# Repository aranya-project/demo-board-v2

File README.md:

# SpiderOak Demo V2 Board

This is a demonstration board for [Aranya
Embedded](https://github.com/aranya-project/aranya-embedded) built around the
ESP32-S3. It provides various peripheral options used by the [Aranya Embedded
demo](https://github.com/aranya-project/aranya-embedded/crates/demo-esp32-s3/).

## Board View

## Assembly Options

The IR transceiver U2 is necessary if you intend ot use IR networking. It uses
the Vishay TFBS4711 which is somewhat pricey, so it has not been included by
default.

The battery jack is a 2mm pitch JST PH connector, and the Qwiic connectors are
1mm pitch JST SH connectors. The RGB LED is a WS2812 5mm LED module. The SD card
slot is a SameSky MSD-4-A, and the USB jack is a GCT USB4105. If you search
around you will find many alternatives for these as they are very commonly used.

A footprint is provided but not populated for reset switch - a SMD 6mm tactile
switch (Omron B3FS or similar). Likewise there is an unpopulated 20pin expansion
header on the back - details on that [below](#test-points-and-expansion).

## Power

Input power comes from either the battery or the USB input. A schottky diode and
a P-channel MOSFET (D5 and Q1) switch power between them and prevent USB power
from backfeeding into the battery. The battery is charged by a standard 500mA
5-pin single-cell lithium linear charge controller (TPS4054/MCP73831/etc), and
LED D1 will light when charging is complete.

The ESP32 is powered by a primary 3.3V regulator (the TLV74333), and all other
devices (IR transceiver, SD card slot, and any Qwiic accessories) are powered
by a secondary 3.3V regulator enabled by a high output on GPIO 47.

Separately, power to the RGB LED is switched via an open drain output on GPIO
40. This pin must be brought low to turn on the P-channel MOSFET controlling
power to the LED. The LED power is connected to input power (either the USB or
battery) directly, so it is not controlled by the accessory power regulator.

### Pin Summary

| GPIO Pin | Function | Operation |
|----------|----------|-----------|
| 47 | Accessory power enable | output, active high |
| 40 | LED power enable | open drain output, active low |

## IR Transceivers

IR1 is connected to UART1 TX/RX on pins on GPIOs 13 and 14, respectively. The IR
transceiver has to be enabled with a low output on GPIO 21.

Enabling IrDA mode requires setting `UART_IRDA_EN` in `UART_CONF0_REG`.
Additionally, to transmit, you need to set `UART_IRDA_TX_EN`. By default, IrDA
mode is half duplex, and `UART_IRDA_TX_EN` needs to be toggled to switch between
transmit and receive modes. To enable both transmit and receive at the same
time, which will echo all transmitted data through the RX line, set
`UART_IRDA_DPLX`.

For reasons I don't understand, the only thing that can be set via IDF APIs is
enabling IrDA mode. All of the other IrDA settings are not available via IDF
APIs, so you will likely have to twiddle the registers directly. In C, this can
be done by including `soc/uart_struct.h` and using the bitfield structs
provided. e.g.

```
UART1.conf0.irda_dplx = 1;
```

### Pin Summary

| GPIO Pin | Function | Operation |
|----------|----------|-----------|
| 13 | Transmit | output |
| 14 | Receive | input |
| 21 | Enable | output, active low |

## Micro SD

The SD card is connected to SPI such that it should be usable directly
through the IOMUX on IOs 35, 36, and 37. CS is connected to GPIO 38.
The slot has card detect functionality, which is connected to GPIO 48.

Additionally, DAT1 and DAT2 (only used in SD mode) are connected to
GPIOs 45 and 39, respectively, so you should theoretically be able to
enable 4-bit SD through the SD/MMC controller.

### Pin Summary (SPI mode)

| GPIO Pin | Function | Operation |
|----------|----------|-----------|
| 36 | SCK | output |
| 35 | MOSI | output |
| 37 | MISO | input |
| 38 | CS | output |

### Pin Summary (SD 1-bit mode)

| GPIO Pin | Function | Operation |
|----------|----------|-----------|
| 36 | CLK | output |
| 35 | CMD | input/output |
| 37 | DAT0 | input/output |
| 38 | CD | input |

### Pin Summary (SD 4-bit mode)

| GPIO Pin | Function | Operation |
|----------|----------|-----------|
| 36 | CLK | output |
| 35 | CMD | input/output |
| 37 | DAT0 | input/output |
| 45 | DAT1 | input/output |
| 39 | DAT2 | input/output |
| 38 | DAT3 | input/output |

### Pin Summary (card detect)

| GPIO Pin | Function | Operation |
|----------|----------|-----------|
| 48 | card detect | input, pull-up, active low |

## Debug LEDs

Three LEDs are hooked up to GPIOs 10-12, and can be used for any purpose.

### Pin Summary

| GPIO Pin | Function | Operation |
|----------|----------|-----------|
| 10 | Debug LED 1 | output, active high |
| 11 | Debug LED 2 | output, active high |
| 12 | Debug LED 3 | output, active high |

## Test points and expansion

The unused GPIOs 1-3, 6-9, 15-18, 42, and 46; the debug LED GPIOs 10-12; as
well as the main and accessory 3.3V regulators; and GND are broken out via a
20-pin 1mm pitch flat flex footprint on the back. You can either install a flat
flex connector or wire directly to the pads.

Test points are provided for VBUS (USB power), V_IN (OR'd power between VBUS and
VBATT), main 3V3, V<sub>acc</sub> (accessory power), SCL/SDA connected to the
Qwiic ports, and SCK, MOSI, MISO, CS, DAT1, DAT2 and CD on the SD card slot.

A three-pin 0.1" header is available for TX, RX, and GND for UART0, and a single
pin header is available for the DO pin on the WS2812 LED module. There are also
0.1" pin headers for the reset switch inside the tactile switch footprint.

## Mechanical

The board is 68mm wide and 42mm tall (2.68 x 1.66 inches). The ESP32-S3 module's
antenna hangs off of the bottom of the board, making the full height 48.4mm
(1.91 inches).

At the top are two M5 sized plated holes meant to accomodate lanyard hooks. They
are centered 5mm from the edges. At the bottom are two more M2.5 holes for any
other mounting needs, centered 3mm from the edges.

A 7x4mm cutout is provided near the battery connector in the top right of the
board. This allows any battery cables to be routed below the board even if the
board is mounted flush against a case.

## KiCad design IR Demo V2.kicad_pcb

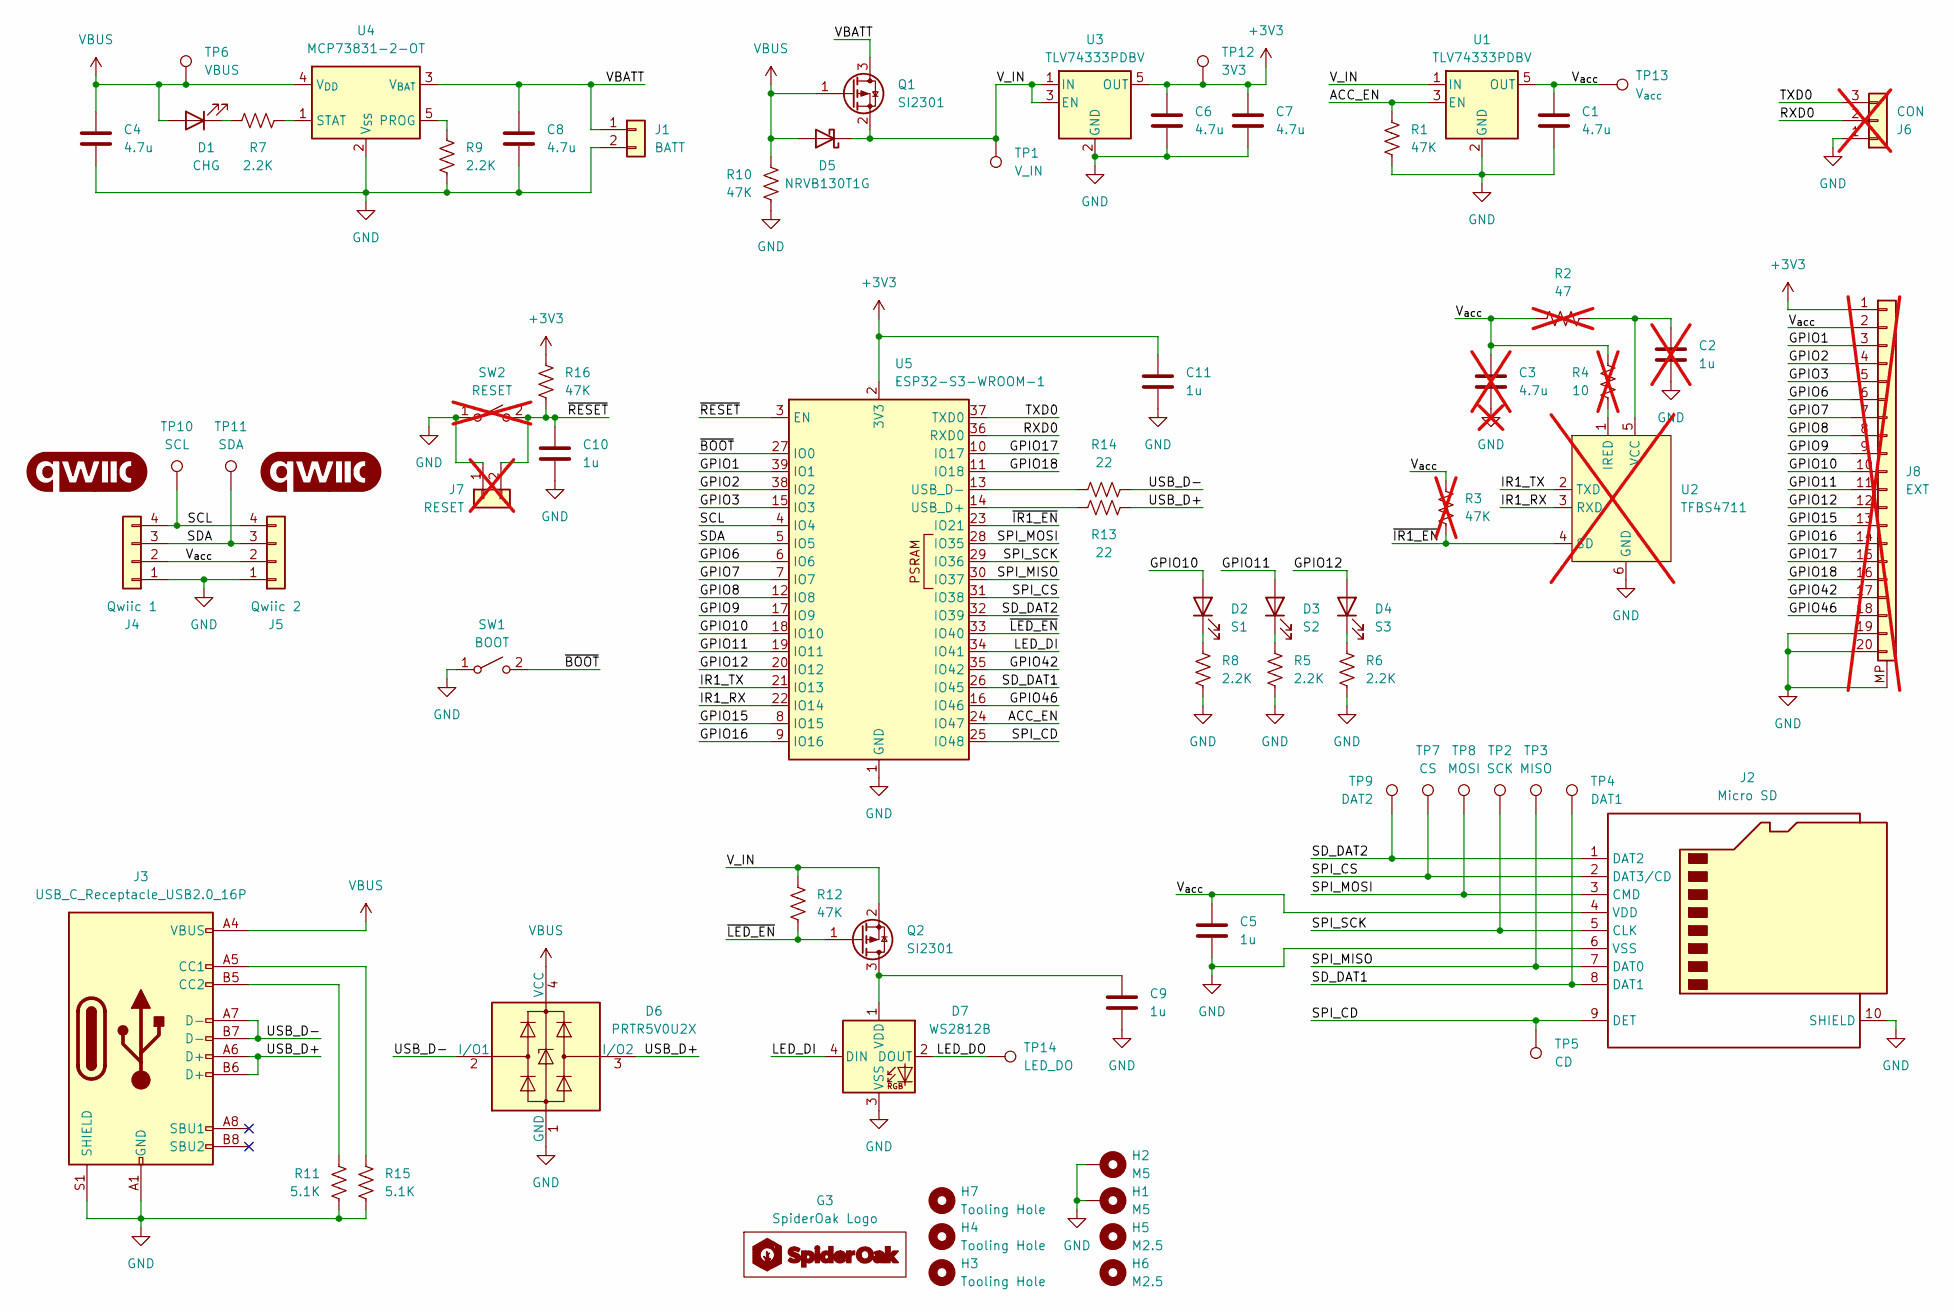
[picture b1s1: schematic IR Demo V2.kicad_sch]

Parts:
C1, C4, C6, C7, C8: 4.7u; C_0805_2012Metric_Pad1.18x1.45mm_HandSolder; MPN CL21A475KPFNNNG; LCSC PN C1779
C2: 1u; C_0805_2012Metric_Pad1.18x1.45mm_HandSolder; MPN CL21B105KBFNNNE; not fitted
C3: 4.7u; C_0805_2012Metric_Pad1.18x1.45mm_HandSolder; MPN CL21A475KPFNNNG; not fitted
C5, C9, C10, C11: 1u; C_0805_2012Metric_Pad1.18x1.45mm_HandSolder; MPN CL21B105KBFNNNE; LCSC PN C28323
D1: CHG; LED_0805_2012Metric; MPN XL-2012SURC; LCSC PN C965812
D2: S1; LED_0805_2012Metric; MPN XL-2012SURC; LCSC PN C965812
D3: S2; LED_0805_2012Metric; MPN XL-2012SURC; LCSC PN C965812
D4: S3; LED_0805_2012Metric; MPN XL-2012SURC; LCSC PN C965812
D5: NRVB130T1G; D_SOD-123; MPN NRVB130T1G; LCSC PN C917121
D6: PRTR5V0U2X; SOT-143; MPN PRTR5V0U2X; LCSC PN C558444
D7: WS2812B; LED_WS2812B_PLCC4_5.0x5.0mm_P3.2mm
G1, G2: qwiic_Logo; qwiic_5.5mm
G3: SpiderOak Logo; SpiderOak_Logo
H1, H2: M5; MountingHole_5.3mm_M5_DIN965_Pad
H3, H4, H7: Tooling Hole; ToolingHole_1.152mm
H5, H6: M2.5; MountingHole_2.7mm_M2.5
J1: BATT; JST_PH_S2B-PH-SM4-TB_1x02-1MP_P2.00mm_Horizontal; MPN WAFER-PH2.0-2PWB; LCSC PN C3029440
J2: Micro SD; MSD-4-A; MPN MSD-4-A; LCSC PN C5454948
J3: USB_C_Receptacle_USB2.0_16P; USB_C_Receptacle_GCT_USB4105-xx-A_16P_TopMnt_Horizontal; MPN USB4105; LCSC PN C2988369
J4: Qwiic 1; JST_SH_SM04B-SRSS-TB_1x04-1MP_P1.00mm_Horizontal; MPN WAFER-SH1.0-4PWB; LCSC PN C3029343
J5: Qwiic 2; JST_SH_SM04B-SRSS-TB_1x04-1MP_P1.00mm_Horizontal; MPN WAFER-SH1.0-4PWB; LCSC PN C3029343
J6: CON; PinHeader_1x03_P2.54mm_Vertical; not fitted
J7: RESET; PinHeader_1x02_P2.54mm_Vertical; not fitted
J8: EXT; TE_2-84953-0_1x20-1MP_P1.0mm_Horizontal; not fitted
Q1, Q2: SI2301; SOT-23; MPN SI2301; LCSC PN C42456911
R1, R10, R12, R16: 47K; R_0805_2012Metric_Pad1.20x1.40mm_HandSolder; MPN RC0805FR-0747KL; LCSC PN C126351
R2: 47; R_0805_2012Metric_Pad1.20x1.40mm_HandSolder; MPN RC0805FR-0722RL; not fitted
R3: 47K; R_0805_2012Metric_Pad1.20x1.40mm_HandSolder; MPN RC0805FR-0747KL; not fitted
R4: 10; R_0805_2012Metric_Pad1.20x1.40mm_HandSolder; MPN RC0805FR-0710RL; not fitted
R5, R6, R7, R8, R9: 2.2K; R_0805_2012Metric_Pad1.20x1.40mm_HandSolder; MPN RC0805FR-072K2L; LCSC PN C114561
R11, R15: 5.1K; R_0805_2012Metric_Pad1.20x1.40mm_HandSolder; MPN RC0805FR-075K1L; LCSC PN C84375
R13, R14: 22; R_0805_2012Metric_Pad1.20x1.40mm_HandSolder; MPN RC0805FR-0722RL; LCSC PN C107702
SW1: BOOT; SW_Push_1P1T_NO_CK_PTS125Sx43PSMTR; MPN TS-1003S-05026; LCSC PN C455219
SW2: RESET; SW_SPST_PTS645; not fitted
TP1: V_IN; TestPoint_Pad_D1.0mm
TP2: SCK; TestPoint_Pad_D1.0mm
TP3: MISO; TestPoint_Pad_D1.0mm
TP4: DAT1; TestPoint_Pad_D1.0mm
TP5: CD; TestPoint_Pad_D1.0mm
TP6: VBUS; TestPoint_Pad_D1.0mm
TP7: CS; TestPoint_Pad_D1.0mm
TP8: MOSI; TestPoint_Pad_D1.0mm
TP9: DAT2; TestPoint_Pad_D1.0mm
TP10: SCL; TestPoint_Pad_D1.0mm
TP11: SDA; TestPoint_Pad_D1.0mm
TP12: 3V3; TestPoint_Pad_D1.0mm
TP13: V_{acc}; TestPoint_Pad_D1.0mm
TP14: LED_DO; TestPoint_THTPad_D2.0mm_Drill1.0mm
U1, U3: TLV74333PDBV; SOT-23-5; MPN TLV74333PDBVR; LCSC PN C408972
U2: TFBS4711; MPN Vishay TFBS4711; not fitted
U4: MCP73831-2-OT; SOT-23-5; MPN TP4054; LCSC PN C5381776
U5: ESP32-S3-WROOM-1; MPN ESP32-S3-WROOM-1-N4R2; LCSC PN C2913203

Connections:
+3V3: C6.1, C7.1, C11.1, J8.1, R16.1, TP12.1, U3.5 (OUT), U5.2 (3V3)
/ACC_EN: R1.1, U1.3 (EN), U5.24 (IO47)
/GPIO1: J8.3, U5.39 (IO1)
/GPIO2: J8.4, U5.38 (IO2)
/GPIO3: J8.5, U5.15 (IO3)
/GPIO6: J8.6, U5.6 (IO6)
/GPIO7: J8.7, U5.7 (IO7)
/GPIO8: J8.8, U5.12 (IO8)
/GPIO9: J8.9, U5.17 (IO9)
/GPIO10: D2.2 (A), J8.10, U5.18 (IO10)
/GPIO11: D3.2 (A), J8.11, U5.19 (IO11)
/GPIO12: D4.2 (A), J8.12, U5.20 (IO12)
/GPIO15: J8.13, U5.8 (IO15)
/GPIO16: J8.14, U5.9 (IO16)
/GPIO17: J8.15, U5.10 (IO17)
/GPIO18: J8.16, U5.11 (IO18)
/GPIO42: J8.17, U5.35 (IO42)
/GPIO46: J8.18, U5.16 (IO46)
/IR1_RX: U2.3 (RXD), U5.22 (IO14)
/IR1_TX: U2.2 (TXD), U5.21 (IO13)
/LED_DI: D7.4 (DIN), U5.34 (IO41)
/LED_DO: D7.2 (DOUT), TP14.1
/RXD0: J6.2, U5.36 (RXD0)
/SCL: J4.4, J5.4, TP10.1, U5.4 (IO4)
/SDA: J4.3, J5.3, TP11.1, U5.5 (IO5)
/SD_DAT1: J2.8 (DAT1), TP4.1, U5.26 (IO45)
/SD_DAT2: J2.1 (DAT2), TP9.1, U5.32 (IO39)
/SPI_CD: J2.9 (DET), TP5.1, U5.25 (IO48)
/SPI_CS: J2.2 (DAT3/CD), TP7.1, U5.31 (IO38)
/SPI_MISO: J2.7 (DAT0), TP3.1, U5.30 (IO37)
/SPI_MOSI: J2.3 (CMD), TP8.1, U5.28 (IO35)
/SPI_SCK: J2.5 (CLK), TP2.1, U5.29 (IO36)
/TXD0: J6.3, U5.37 (TXD0)
/USB_D+: D6.3 (I/O2), J3.A6 (D+), J3.B6 (D+), R13.2
/USB_D-: D6.2 (I/O1), J3.A7 (D-), J3.B7 (D-), R14.2
/VBATT: C8.1, J1.1, Q1.3 (D), U4.3 (V_{BAT})
/V_IN: D5.1 (K), Q1.2 (S), Q2.2 (S), R12.1, TP1.1, U1.1 (IN), U3.1 (IN), U3.3 (EN)
/V_{acc}: C1.1, C3.1, C5.1, J2.4 (VDD), J4.2, J5.2, J8.2, R2.1, R3.1, R4.1, TP13.1, U1.5 (OUT)
/~BOOT: SW1.2 (B), U5.27 (IO0)
/~IR1_EN: R3.2, U2.4 (SD), U5.23 (IO21)
/~LED_EN: Q2.1 (G), R12.2, U5.33 (IO40)
/~RESET: C10.1, J7.2, R16.2, SW2.2 (B), U5.3 (EN)
GND: C1.2, C2.2, C3.2, C4.2, C5.2, C6.2, C7.2, C8.2, C9.2, C10.2, C11.2, D6.1 (GND), D7.3 (VSS), H1.1, H2.1, J1.2, J2.6 (VSS), J2.10 (SHIELD), J3.A1 (GND), J3.A12 (GND), J3.B1 (GND), J3.B12 (GND), J3.S1 (SHIELD), J4.1, J5.1, J6.1, J7.1, J8.19, J8.20, J8.MP, R1.2, R5.2, R6.2, R8.2, R9.2, R10.2, R11.2, R15.2, SW1.1 (A), SW2.1 (A), U1.2 (GND), U2.6 (GND), U3.2 (GND), U4.2 (V_{SS}), U5.1 (GND), U5.40 (GND), U5.41 (GND)
unnamed: D1.1 (K), R7.1
unnamed: D2.1 (K), R8.1
unnamed: D3.1 (K), R5.1
unnamed: D4.1 (K), R6.1
unnamed: C9.1, D7.1 (VDD), Q2.3 (D)
unnamed: J3.A5 (CC1), R15.1
unnamed: J3.B5 (CC2), R11.1
unnamed: R4.2, U2.1 (IRED)
unnamed: C2.1, R2.2, U2.5 (VCC)
unnamed: R9.1, U4.5 (PROG)
unnamed: R7.2, U4.1 (STAT)
unnamed: R13.1, U5.14 (USB_D+)
unnamed: R14.1, U5.13 (USB_D-)
VBUS: C4.1, D1.2 (A), D5.2 (A), D6.4 (VCC), J3.A4 (VBUS), J3.A9 (VBUS), J3.B4 (VBUS), J3.B9 (VBUS), Q1.1 (G), R10.1, TP6.1, U4.4 (V_{DD})

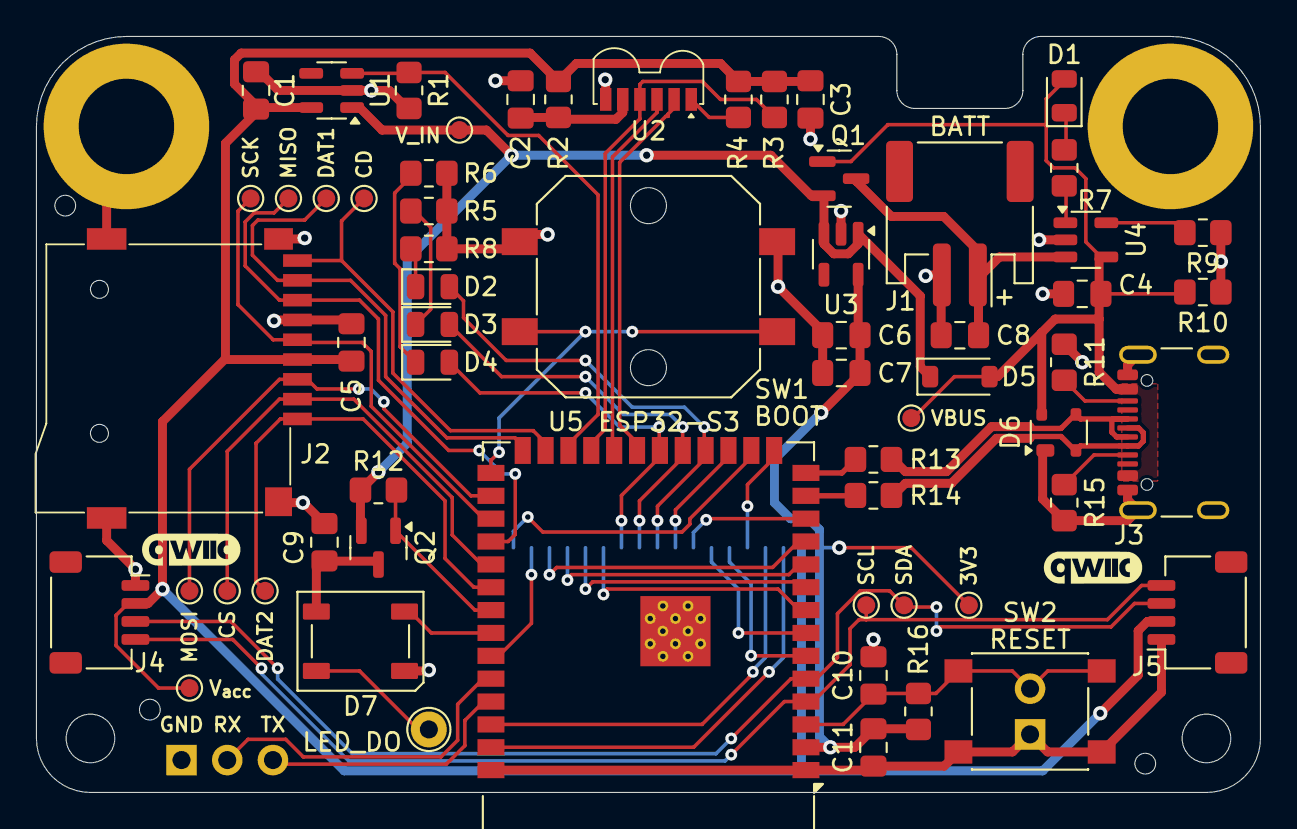
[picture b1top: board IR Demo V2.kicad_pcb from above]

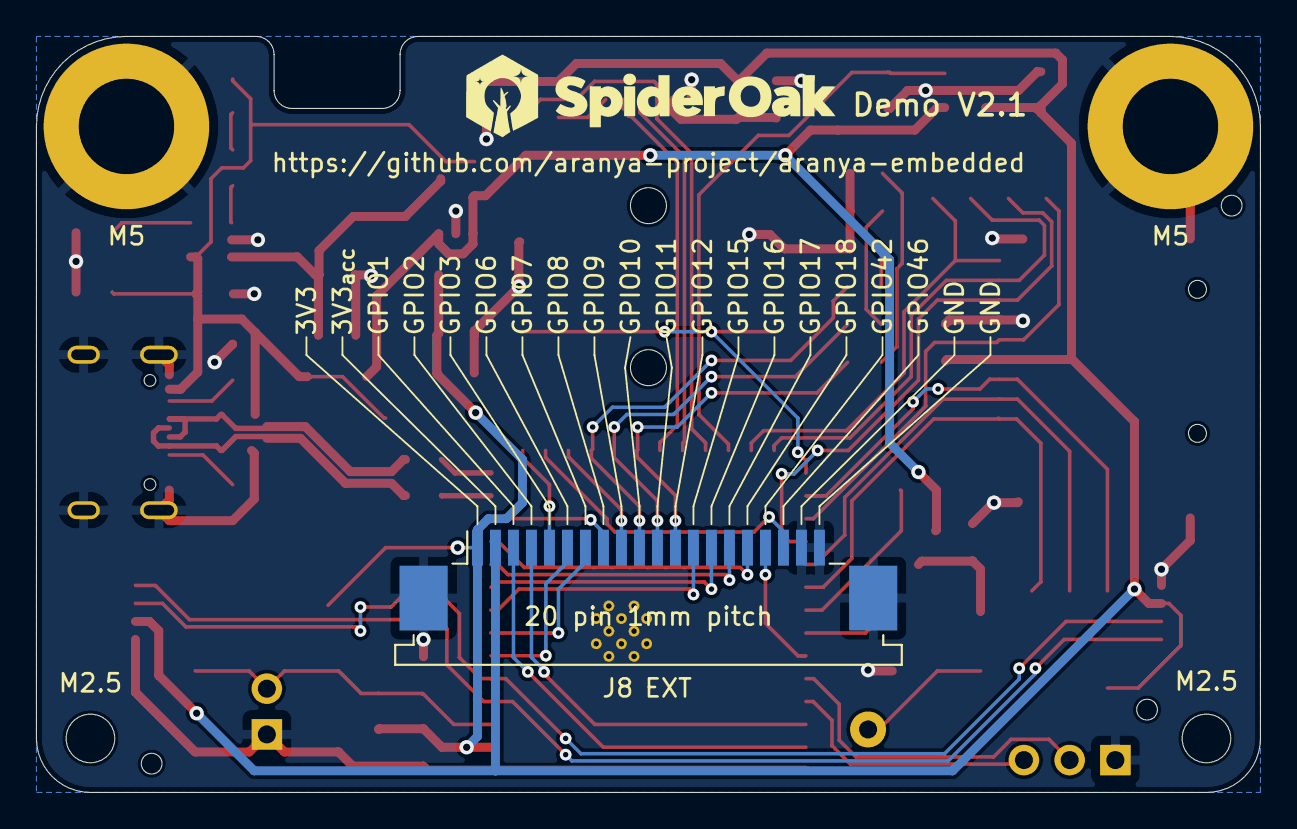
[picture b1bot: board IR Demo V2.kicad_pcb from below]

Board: 2 copper layers, 68.0 x 42.0 mm, 75 parts (2 on the bottom side), 57 nets.

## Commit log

2025-06-18 WIP version 2.1
2025-06-18 Works better when you add the images
